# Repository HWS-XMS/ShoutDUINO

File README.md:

# ShoutDUINO

Attention: I still want to place and route the unity gain buffer on the feedback path.
That's not yet in the prod. files.

Arduino-based, safe-ish, EMFI tool, at lower cost.

The board charges a capacitor to a programmable high voltage, then discharges it
through an injection coil on a trigger event. Trigger timing can come from the
host over UART (soft trigger) or from an external trigger input, with host-side
tooling for parameter sweeps.

## Status

**We are currently adding a unity gain buffer to the feedback, which improves
voltage readback.** The buffer isolates the high-voltage divider from the ADC
input, so loading by the converter no longer pulls the measured value down.

This change is in progress and is not yet in the schematic.

## Repository layout

| Path | Contents |
| --- | --- |
| `PCB/` | KiCad project. Root sheet `shoutduino.kicad_sch`, with `charger`, `discharger`, `leds` and `temperature` sub-sheets. |
| `firmware/` | Arduino firmware for the on-board microcontroller. |
| `python/` | Host-side CLI, calibration and experiment scripts. |
| `docs/datasheets/` | Datasheets for the main devices used on the board. |
| `PCB/shoutduino.pretty/`, `PCB/shoutduino.kicad_sym` | Project-local footprint and symbol libraries for the non-stock parts, registered via `PCB/fp-lib-table` and `PCB/sym-lib-table`. |
| `production/` | Generated fabrication output (gerbers, BOM, placement). |
| `DelayUnit/` | Submodule: FPGA-based delay unit used to place the trigger pulse. |

## Hardware

Key devices in the signal chain:

- **LT3751** — flyback controller driving the high-voltage capacitor charger.
- **AD5293** — digital potentiometer setting the charge voltage target.
- **MCP3201** — 12-bit SPI ADC for voltage readback.
- **MCP601** (`U12`) — op-amp in the charger feedback path.
- **TMP117** — temperature monitoring.

The KiCad files are saved in **KiCad 10** format.

## Firmware

Build with `arduino-cli` via the provided Makefile:

```sh
cd firmware
make uno-r4-minima     # or: uno-r4-wifi
make flash             # compile and upload
make detect            # list connected boards
```

Pulse width is constrained to **10–200 ns**. The firmware rejects any soft-trigger
width outside that window, because pulses longer than 200 ns can destroy the
discharge circuit. Note that this guard only covers the UART soft-trigger path —
an externally supplied trigger pulse is not clamped by the firmware.

## Host tooling

```sh
cd python
pip install -r requirements.txt
python emfi_cli.py /dev/ttyACM0     # interactive control
python calibrate.py                 # pot position -> voltage calibration
python experiment.py                # voltage/delay parameter sweep
```

## Cloning

The repository uses a submodule:

```sh
git clone --recurse-submodules https://github.com/HWS-XMS/ShoutDUINO.git
```

## Known issues

- `make uno` (classic AVR Uno) does not compile: `temperature_controller.cpp`
  uses `INPUT_PULLDOWN`, which the AVR core does not provide. Only the UNO R4
  targets build. `make test-all` fails for this reason.

## Safety

This board generates and stores high voltage. The capacitor can hold a dangerous
charge after power is removed. Do not handle the board while it is charged.

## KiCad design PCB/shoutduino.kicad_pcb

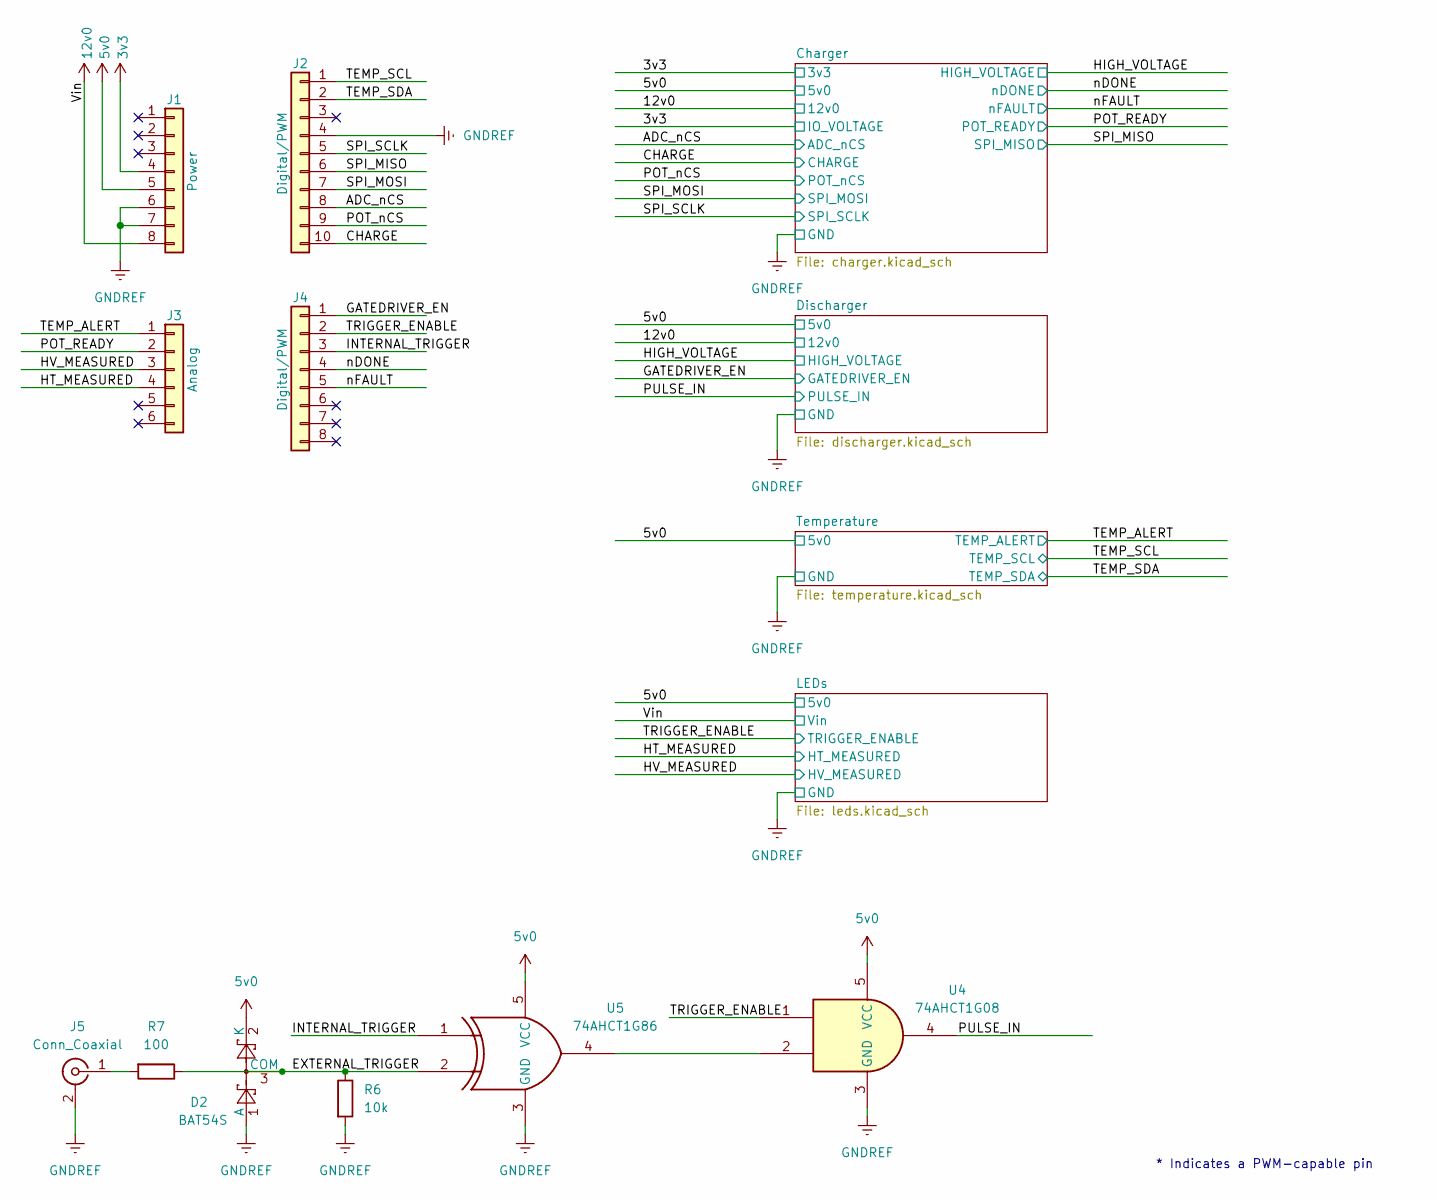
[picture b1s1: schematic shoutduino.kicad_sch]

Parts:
D2: BAT54S; SOT-23
J1: Power; PinSocket_1x08_P2.54mm_Vertical
J2: Digital/PWM; PinSocket_1x10_P2.54mm_Vertical
J3: Analog; PinSocket_1x06_P2.54mm_Vertical
J4: Digital/PWM; PinSocket_1x08_P2.54mm_Vertical
J5: Conn_Coaxial; SMA_Amphenol_132289_EdgeMount
R6: 10k; R_0402_1005Metric
R7: 100; R_0402_1005Metric
U4: 74AHCT1G08; SOT-23-5
U5: 74AHCT1G86; SOT-23-5

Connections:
5v0: D2.2 (K), J1.5, U4.5 (VCC), U5.5 (VCC); also elsewhere on the board
12v0: J1.8; also elsewhere on the board
/ADC_nCS: J2.8; also elsewhere on the board
/CHARGE: J2.10; also elsewhere on the board
/EXTERNAL_TRIGGER: D2.3 (COM), R6.1, R7.1, U5.2
/GATEDRIVER_EN: J4.1; also elsewhere on the board
/HT_MEASURED: J3.4; also elsewhere on the board
/HV_MEASURED: J3.3; also elsewhere on the board
/INTERNAL_TRIGGER: J4.3, U5.1
/POT_READY: J3.2; also elsewhere on the board
/POT_nCS: J2.9; also elsewhere on the board
/PULSE_IN: U4.4; also elsewhere on the board
/SPI_MISO: J2.6; also elsewhere on the board
/SPI_MOSI: J2.7; also elsewhere on the board
/SPI_SCLK: J2.5; also elsewhere on the board
/TEMP_ALERT: J3.1; also elsewhere on the board
/TEMP_SCL: J2.1; also elsewhere on the board
/TEMP_SDA: J2.2; also elsewhere on the board
/TRIGGER_ENABLE: J4.2, U4.1; also elsewhere on the board
/nDONE: J4.4; also elsewhere on the board
/nFAULT: J4.5; also elsewhere on the board
GNDREF: D2.1 (A), J1.6, J1.7, J2.4, J5.2 (Ext), R6.2, U4.3 (GND), U5.3 (GND); also elsewhere on the board
unnamed: J5.1 (In), R7.2
unnamed: U4.2, U5.4

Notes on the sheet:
* Indicates a PWM-capable pin

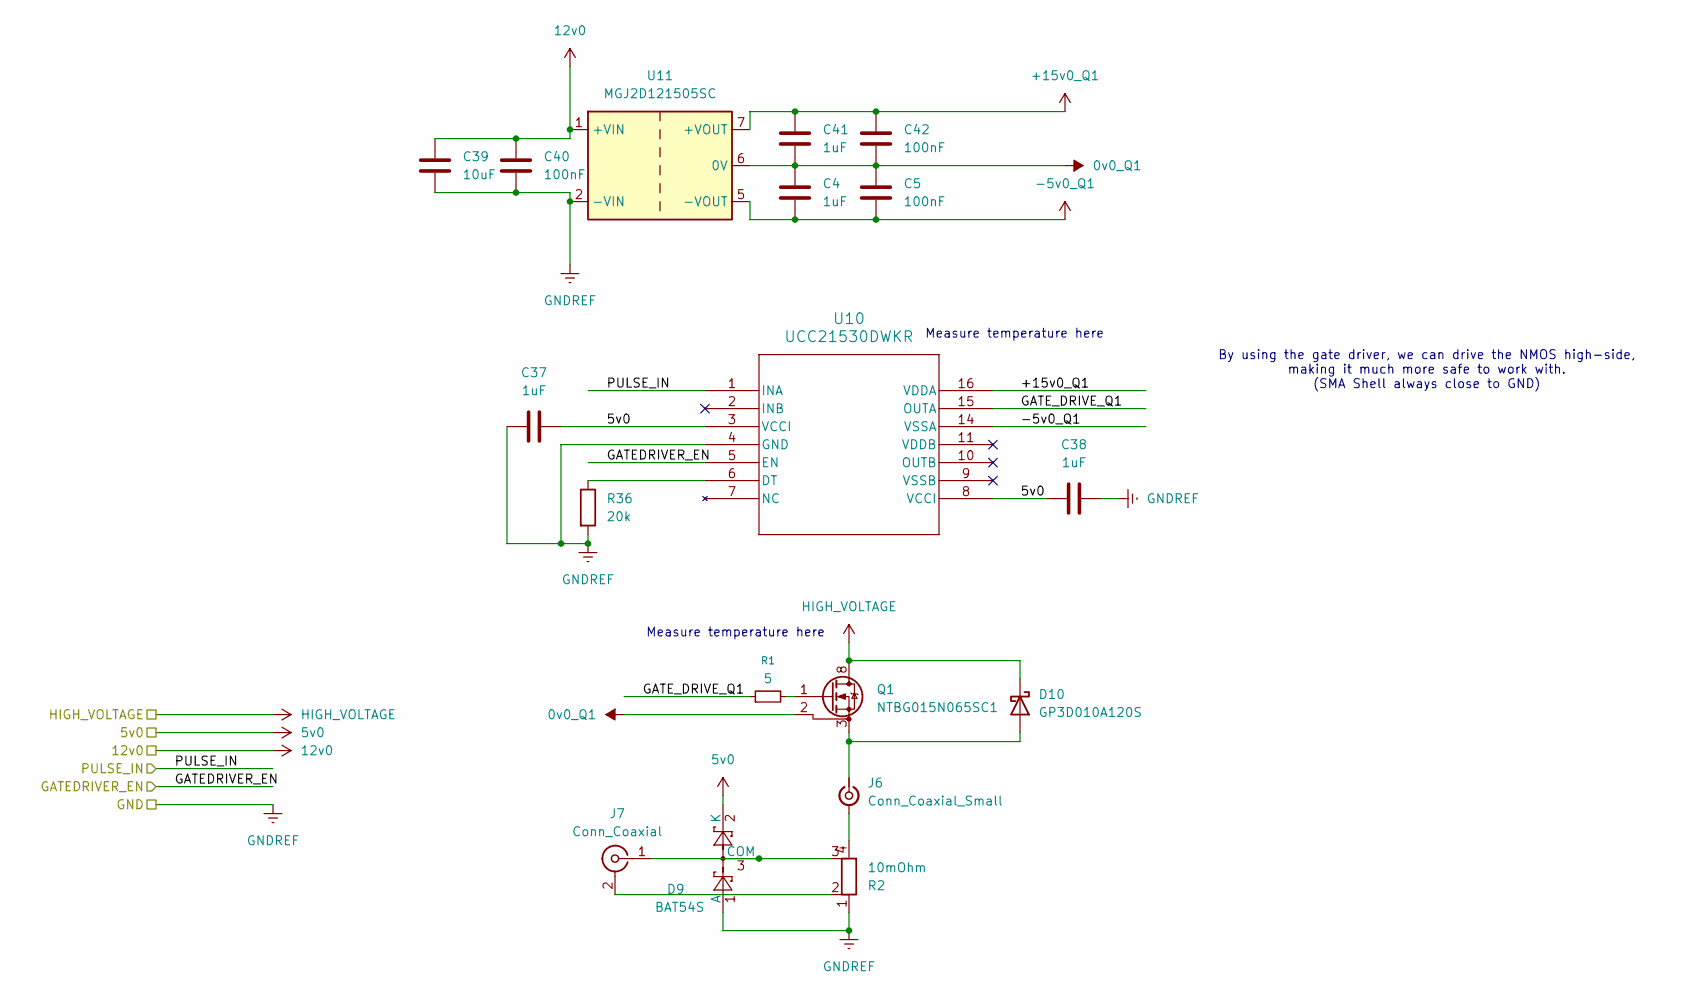
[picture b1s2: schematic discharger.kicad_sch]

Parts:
C4, C37, C38, C41: 1uF; C_0603_1608Metric
C5, C40, C42: 100nF; C_0603_1608Metric
C39: 10uF; C_0603_1608Metric
D9: BAT54S; SOT-23
D10: GP3D010A120S; D_SMC
J6: Conn_Coaxial_Small; SMA_Amphenol_132289_EdgeMount
J7: Conn_Coaxial; U.FL_Molex_MCRF_73412-0110_Vertical
Q1: NTBG015N065SC1; TO-263-7_TabPin8
R1: 5; R_0603_1608Metric
R2: 10mOhm; FC4L110_OHM
R36: 20k; R_0603_1608Metric
U10: UCC21530DWKR; SOIC14_7P6X10P5_TEX
U11: MGJ2D121505SC; Converter_DCDC_Murata_MGJ2DxxxxxxSC_THT

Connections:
0v0_Q1: C4.1, C5.1, C41.2, C42.2, Q1.2 (DS), U11.6 (0V)
5v0: C37.2, C38.2, D9.2 (K), U10.3 (VCCI), U10.8 (VCCI); also elsewhere on the board
12v0: C39.1, C40.1, U11.1 (+VIN); also elsewhere on the board
+15v0_Q1: C41.1, C42.1, U10.16 (VDDA), U11.7 (+VOUT)
-5v0_Q1: C4.2, C5.2, U10.14 (VSSA), U11.5 (-VOUT)
/Discharger/GATE_DRIVE_Q1: R1.1, U10.15 (OUTA)
/GATEDRIVER_EN: U10.5 (EN); also elsewhere on the board
/PULSE_IN: U10.1 (INA); also elsewhere on the board
GNDREF: C37.1, C38.1, C39.2, C40.2, D9.1 (A), R2.1, R36.2, U10.4 (GND), U11.2 (-VIN); also elsewhere on the board
HIGH_VOLTAGE: D10.1 (K), Q1.8 (D); also elsewhere on the board
unnamed: D9.3 (COM), J7.1 (In), R2.3
unnamed: D10.2 (A), J6.1 (In), Q1.3 (S), Q1.4 (S), Q1.5 (S), Q1.6 (S), Q1.7 (S)
unnamed: J6.2 (Ext), R2.4
unnamed: J7.2 (Ext), R2.2
unnamed: Q1.1 (G), R1.2
unnamed: R36.1, U10.6 (DT)

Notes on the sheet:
Measure temperature here
By using the gate driver, we can drive the NMOS high-side, making it much more safe to work with. (SMA Shell always close to GND)

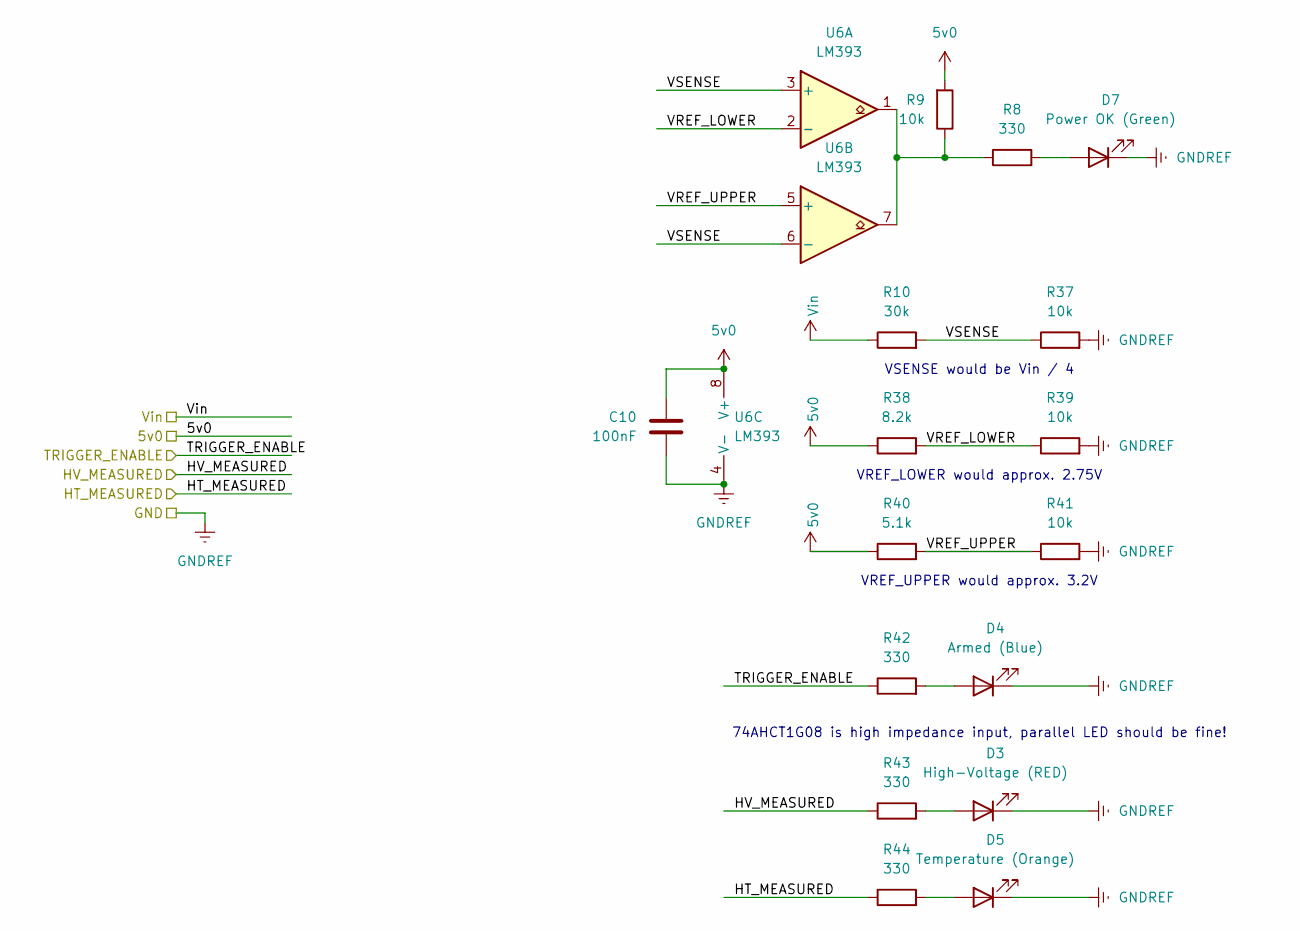
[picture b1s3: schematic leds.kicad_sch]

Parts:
C10: 100nF; C_0603_1608Metric
D3: High-Voltage (RED); LED_0805_2012Metric
D4: Armed (Blue); LED_0805_2012Metric
D5: Temperature (Orange); LED_0805_2012Metric
D7: Power OK (Green); LED_0805_2012Metric
R8, R42, R43, R44: 330; R_0603_1608Metric
R9, R37, R39, R41: 10k; R_0603_1608Metric
R10: 30k; R_0603_1608Metric
R38: 8.2k; R_0603_1608Metric
R40: 5.1k; R_0603_1608Metric
U6: LM393; SOIC-8_3.9x4.9mm_P1.27mm

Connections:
5v0: C10.1, R9.2, R38.1, R40.1, U6.8 (V+); also elsewhere on the board
12v0: R10.1; also elsewhere on the board
/HT_MEASURED: R44.1; also elsewhere on the board
/HV_MEASURED: R43.1; also elsewhere on the board
/LEDs/VREF_LOWER: R38.2, R39.1, U6.2 (-)
/LEDs/VREF_UPPER: R40.2, R41.1, U6.5 (+)
/LEDs/VSENSE: R10.2, R37.1, U6.3 (+), U6.6 (-)
/TRIGGER_ENABLE: R42.1; also elsewhere on the board
GNDREF: C10.2, D3.1 (K), D4.1 (K), D5.1 (K), D7.1 (K), R37.2, R39.2, R41.2, U6.4 (V-); also elsewhere on the board
unnamed: D3.2 (A), R43.2
unnamed: D4.2 (A), R42.2
unnamed: D5.2 (A), R44.2
unnamed: D7.2 (A), R8.2
unnamed: R8.1, R9.1, U6.1, U6.7

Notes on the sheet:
VREF_LOWER would approx. 2.75V
74AHCT1G08 is high impedance input, parallel LED should be fine!
VREF_UPPER would approx. 3.2V
VSENSE would be Vin / 4

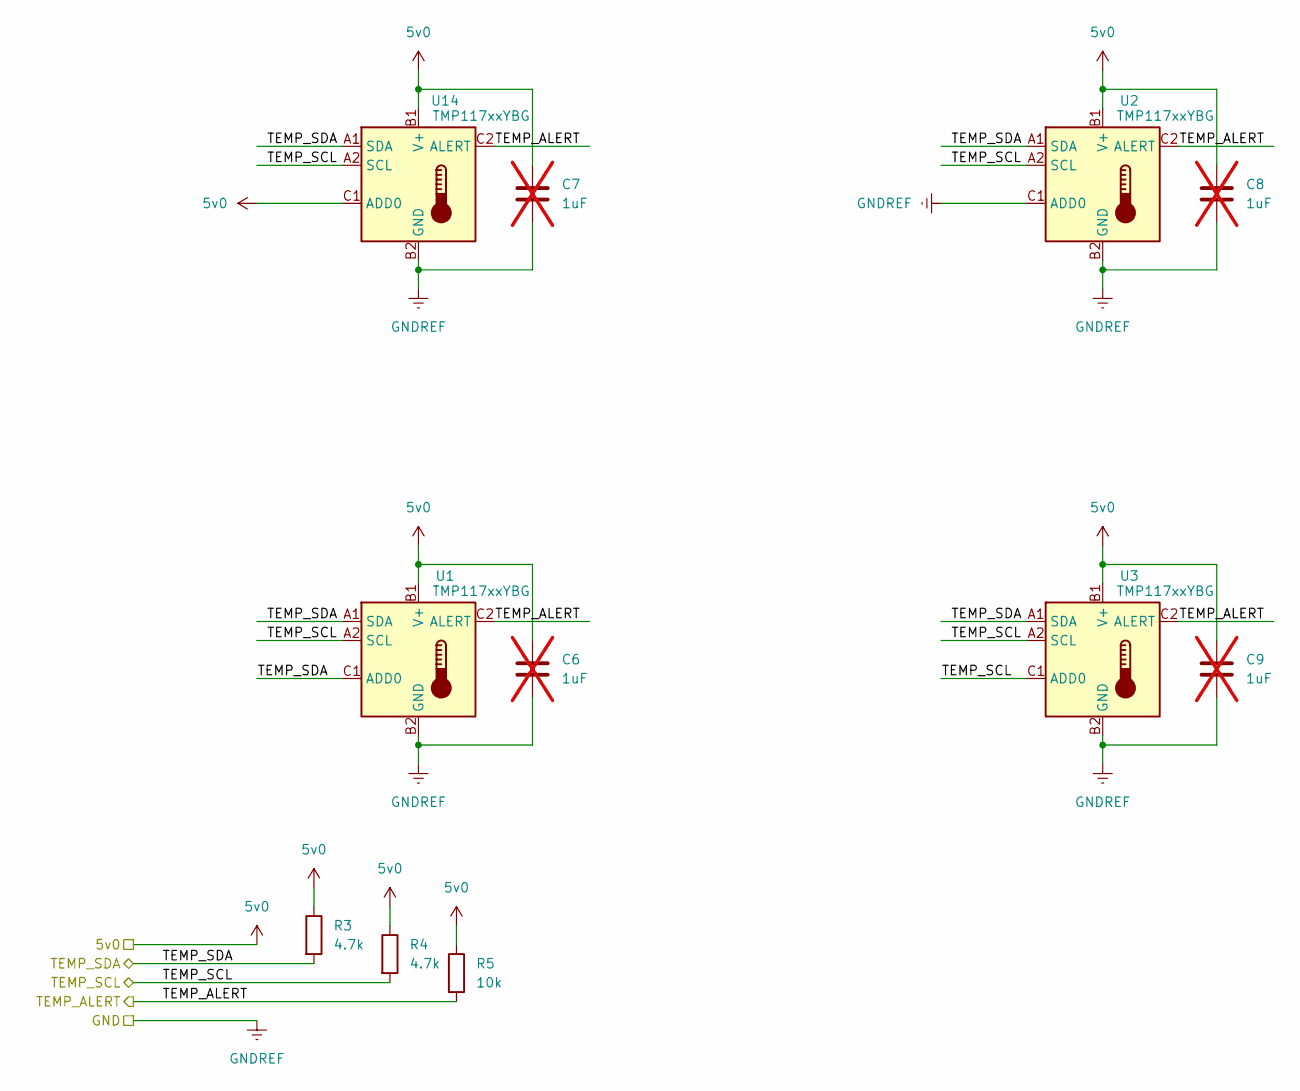
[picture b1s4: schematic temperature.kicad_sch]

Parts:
C6, C7, C8, C9: 1uF; C_0603_1608Metric; not fitted
R3, R4: 4.7k; R_0603_1608Metric
R5: 10k; R_0603_1608Metric
U1, U2, U3, U14: TMP117xxYBG; Texas_DSBGA-6_0.95x1.488mm_Layout2x3_P0.4mm

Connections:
5v0: C6.2, C7.2, C8.2, C9.2, R3.1, R4.1, R5.1, U1.B1 (V+), U2.B1 (V+), U3.B1 (V+), U14.B1 (V+), U14.C1 (ADD0); also elsewhere on the board
/TEMP_ALERT: R5.2, U1.C2 (ALERT), U2.C2 (ALERT), U3.C2 (ALERT), U14.C2 (ALERT); also elsewhere on the board
/TEMP_SCL: R4.2, U1.A2 (SCL), U2.A2 (SCL), U3.A2 (SCL), U3.C1 (ADD0), U14.A2 (SCL); also elsewhere on the board
/TEMP_SDA: R3.2, U1.A1 (SDA), U1.C1 (ADD0), U2.A1 (SDA), U3.A1 (SDA), U14.A1 (SDA); also elsewhere on the board
GNDREF: C6.1, C7.1, C8.1, C9.1, U1.B2 (GND), U2.B2 (GND), U2.C1 (ADD0), U3.B2 (GND), U14.B2 (GND); also elsewhere on the board

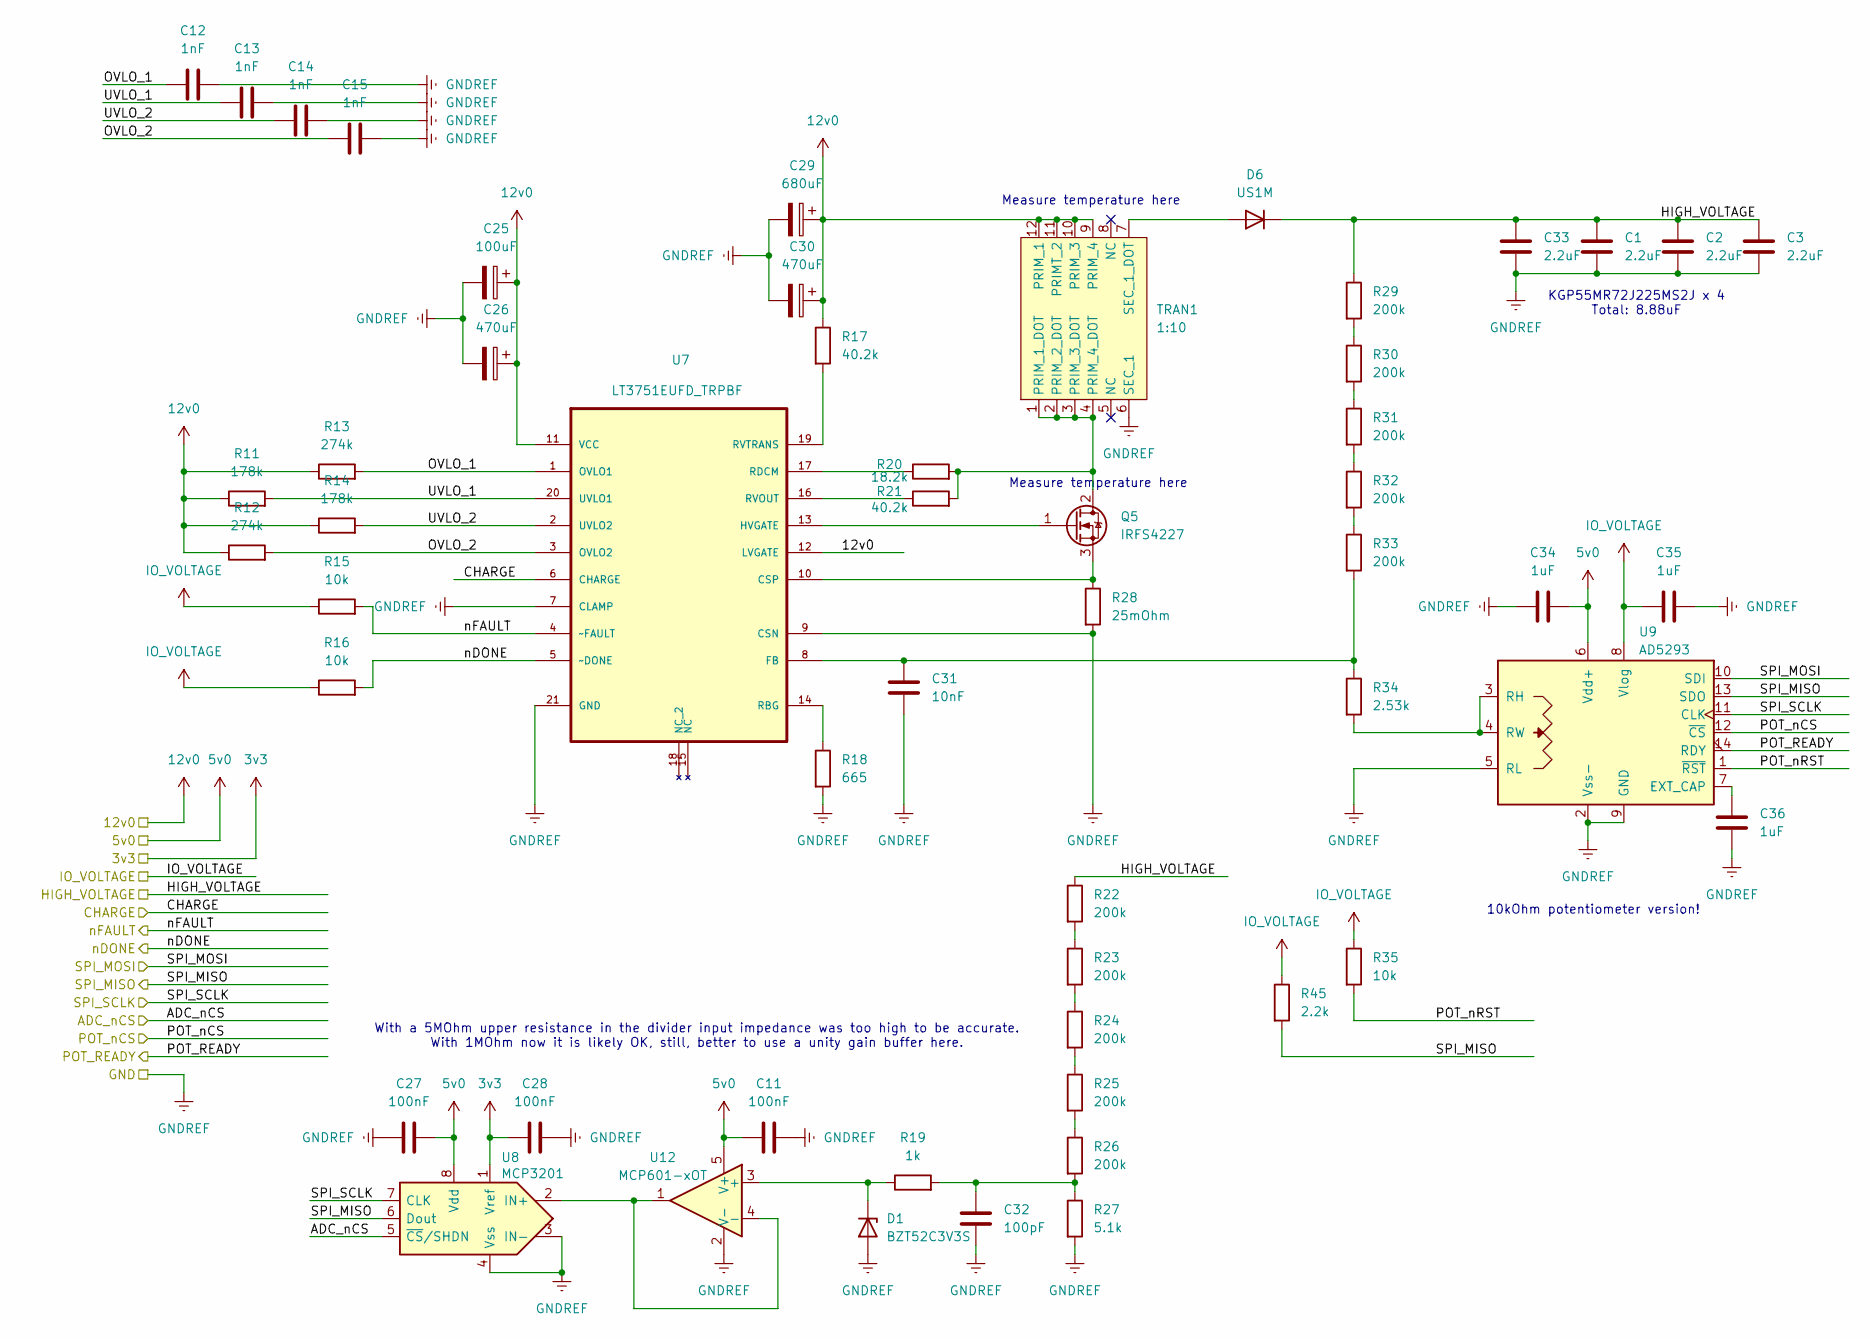
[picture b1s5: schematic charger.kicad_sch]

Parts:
C1, C2, C3, C33: 2.2uF; C_2220_5750Metric
C11, C27, C28: 100nF; C_0603_1608Metric
C12, C13, C14, C15: 1nF; C_0402_1005Metric
C25: 100uF; CP_Radial_D6.3mm_P2.50mm
C26, C30: 470uF; CP_Radial_D8.0mm_P3.50mm
C29: 680uF; CP_Radial_D10.0mm_P5.00mm
C31: 10nF; C_0603_1608Metric
C32: 100pF; C_0603_1608Metric
C34, C35, C36: 1uF; C_0603_1608Metric
D1: BZT52C3V3S; D_SOD-323
D6: US1M; D_SMA
Q5: IRFS4227; TO-263-2
R11, R14: 178k; R_0402_1005Metric
R12, R13: 274k; R_0402_1005Metric
R15, R16: 10k; R_0402_1005Metric
R17: 40.2k; R_0402_1005Metric
R18: 665; R_0603_1608Metric
R19: 1k; R_0603_1608Metric
R20: 18.2k; R_0603_1608Metric
R21: 40.2k; R_0603_1608Metric
R22, R23, R24, R25, R26, R29, R30, R31, R32, R33: 200k; R_0805_2012Metric
R27: 5.1k; R_0805_2012Metric
R28: 25mOhm; R_2512_6332Metric_Pad1.40x3.35mm_HandSolder
R34: 2.53k; R_0805_2012Metric
R35: 10k; R_0603_1608Metric
R45: 2.2k; R_0603_1608Metric
TRAN1: 1:10; GA3460-BL
U7: LT3751EUFD_TRPBF; QFN50P400X500X80-21N; MPN LT3751EUFD#PBF
U8: MCP3201; SOIC-8_3.9x4.9mm_P1.27mm
U9: AD5293; TSSOP-14_4.4x5mm_P0.65mm
U12: MCP601-xOT; SOT-23-5

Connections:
5v0: C11.2, C27.2, C34.2, U8.8 (Vdd), U9.6 (Vdd+), U12.5 (V+); also elsewhere on the board
12v0: C25.1, C26.1, C29.1, C30.1, R11.1, R12.1, R13.1, R14.1, R17.1, TRAN1.9 (PRIM_4), TRAN1.10 (PRIM_3), TRAN1.11 (PRIMT_2), TRAN1.12 (PRIM_1), U7.11 (VCC), U7.12 (LVGATE); also elsewhere on the board
/ADC_nCS: U8.5 (~CS/SHDN); also elsewhere on the board
/CHARGE: U7.6 (CHARGE); also elsewhere on the board
/Charger/OVLO_1: C12.1, R13.2, U7.1 (OVLO1)
/Charger/OVLO_2: C15.1, R12.2, U7.3 (OVLO2)
/Charger/POT_nRST: R35.2, U9.1 (~RST)
/Charger/UVLO_1: C13.1, R11.2, U7.20 (UVLO1)
/Charger/UVLO_2: C14.1, R14.2, U7.2 (UVLO2)
/POT_READY: U9.14 (RDY); also elsewhere on the board
/POT_nCS: U9.12 (~CS); also elsewhere on the board
/SPI_MISO: R45.2, U8.6 (Dout), U9.13 (SDO); also elsewhere on the board
/SPI_MOSI: U9.10 (SDI); also elsewhere on the board
/SPI_SCLK: U8.7 (CLK), U9.11 (CLK); also elsewhere on the board
/nDONE: R16.2, U7.5 (~DONE); also elsewhere on the board
/nFAULT: R15.2, U7.4 (~FAULT); also elsewhere on the board
GNDREF: C1.2, C2.2, C3.2, C11.1, C12.2, C13.2, C14.2, C15.2, C25.2, C26.2, C27.1, C28.1, C29.2, C30.2, C31.2, C32.2, C33.2, C34.1, C35.1, C36.1, D1.2 (A), R18.2, R27.2, R28.2, TRAN1.6 (SEC_1), U7.7 (CLAMP), U7.9 (CSN), U7.21 (GND), U8.3 (IN-), U8.4 (Vss), U9.2 (Vss-), U9.5 (RL), U9.9 (GND), U12.2 (V-); also elsewhere on the board
HIGH_VOLTAGE: C1.1, C2.1, C3.1, C33.1, D6.1 (K), R22.1, R29.1; also elsewhere on the board
unnamed: C32.1, R19.2, R26.2, R27.1
unnamed: D1.1 (K), R19.1, U12.3 (+)
unnamed: D6.2 (A), TRAN1.7 (SEC_1_DOT)
unnamed: Q5.2 (D), R20.2, R21.2, TRAN1.1 (PRIM_1_DOT), TRAN1.2 (PRIM_2_DOT), TRAN1.3 (PRIM_3_DOT), TRAN1.4 (PRIM_4_DOT)
unnamed: Q5.1 (G), U7.13 (HVGATE)
unnamed: Q5.3 (S), R28.1, U7.10 (CSP)
unnamed: R22.2, R23.1
unnamed: R23.2, R24.1
unnamed: R24.2, R25.1
unnamed: R25.2, R26.1
unnamed: R29.2, R30.1
unnamed: R30.2, R31.1
unnamed: R31.2, R32.1
unnamed: R32.2, R33.1
unnamed: C31.1, R33.2, R34.1, U7.8 (FB)
unnamed: R18.1, U7.14 (RBG)
unnamed: R20.1, U7.17 (RDCM)
unnamed: R21.1, U7.16 (RVOUT)
unnamed: R17.2, U7.19 (RVTRANS)
unnamed: C36.2, U9.7 (EXT_CAP)
unnamed: R34.2, U9.3 (RH), U9.4 (RW)
unnamed: U8.2 (IN+), U12.1, U12.4 (-)

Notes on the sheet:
KGP55MR72J225MS2J x 4 Total: 8.88uF
With a 5MOhm upper resistance in the divider input impedance was too high to be accurate. With 1MOhm now it is likely OK, still, better to use a unity gain buffer here.
Measure temperature here
10kOhm potentiometer version!

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
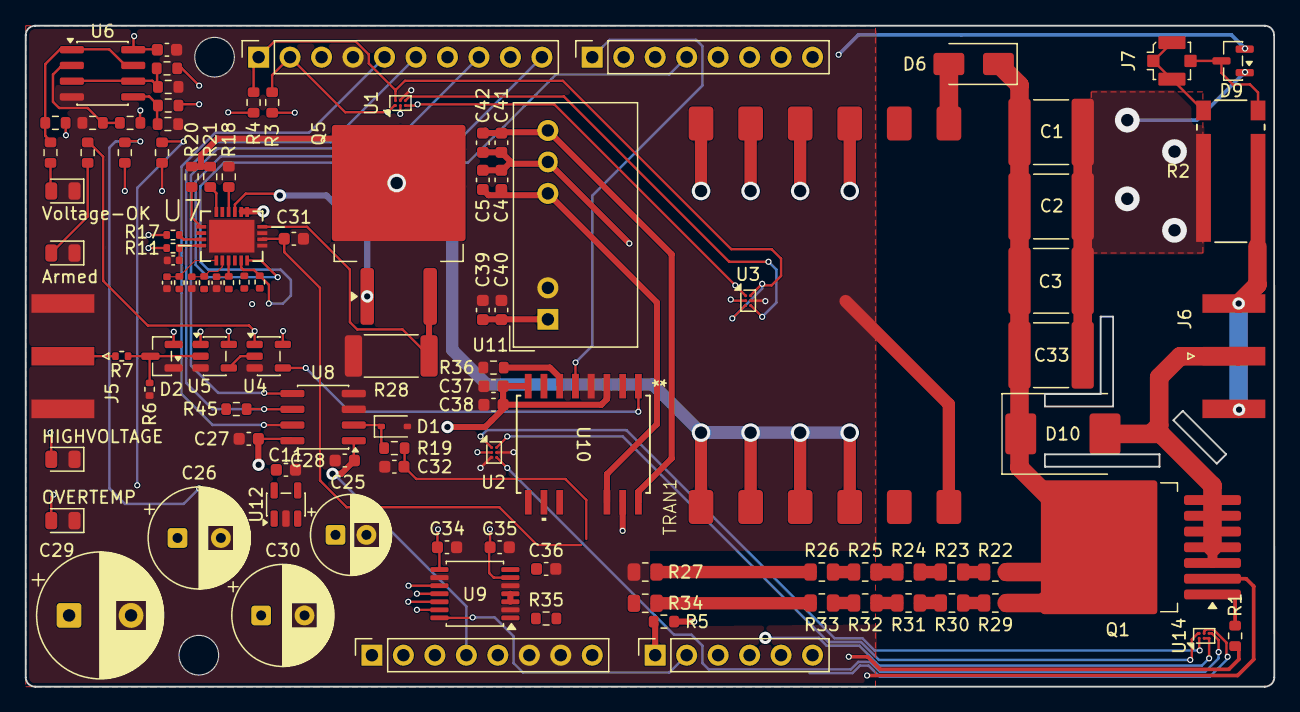
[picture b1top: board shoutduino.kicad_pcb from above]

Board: 4 copper layers, 100.8 x 53.3 mm, 108 parts (0 on the bottom side), 71 nets.

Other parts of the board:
MH1, MH2: MountingHole_3.2mm

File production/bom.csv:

Designator,Footprint,Quantity,Value,LCSC Part #
"C1, C2, C3, C33",2220,4,2.2uF,
"C10, C27, C28, C40, C42, C5",0603,6,100nF,
C25,CP_Radial_D6.3mm_P2.50mm,1,100uF,
"C26, C30",CP_Radial_D8.0mm_P3.50mm,2,470uF,
C29,CP_Radial_D10.0mm_P5.00mm,1,680uF,
C31,0603,1,10nF,
C32,0603,1,100pF,
"C34, C35, C36, C37, C38, C4, C41",0603,7,1uF,
C39,0603,1,10uF,
D1,D_SOD-323,1,BZT52C3V3S,
"D2, D9",SOT-23,2,BAT54S,
D3,0805,1,High-Voltage (RED),
D4,0805,1,Armed (Blue),
D5,0805,1,Temperature (Orange),
"D6, D8",D_SMA,2,US1M,
D7,0805,1,Power OK (Green),
J1,PinSocket_1x08_P2.54mm_Vertical,1,Power,
J2,PinSocket_1x10_P2.54mm_Vertical,1,Digital/PWM,
J3,PinSocket_1x06_P2.54mm_Vertical,1,Analog,
J4,PinSocket_1x08_P2.54mm_Vertical,1,Digital/PWM,
J5,SMA_Amphenol_132289_EdgeMount,1,Conn_Coaxial,
J6,SMA_Amphenol_132289_EdgeMount,1,Conn_Coaxial_Small,
J7,U.FL_Molex_MCRF_73412-0110_Vertical,1,Conn_Coaxial,
Q1,TO-263-7_TabPin8,1,NTBG015N065SC1,
Q5,TO-263-2,1,IRFS4227,
R1,0603,1,10,
R10,0603,1,30k,
"R11, R14",0402,2,178k,
"R12, R13",0402,2,274k,
"R15, R16, R6",0402,3,10k,
R17,0402,1,40.2k,
R18,0603,1,665,
R19,0603,1,1k,
R2,FC4L110_OHM,1,10mOhm,
R20,0603,1,18.2k,
R21,0603,1,40.2k,
"R22, R23, R24, R25, R26, R29, R30, R31, R32, R33",0805,10,1M,
R27,0805,1,25k,
R28,2512,1,25mOhm,
"R3, R4",0603,2,4.7k,
R34,0805,1,12.1k,
"R35, R37, R39, R41, R5, R9",0603,6,10k,
R36,0603,1,20k,
R38,0603,1,8.2k,
R40,0603,1,5.1k,
"R42, R43, R44, R8",0603,4,330,
R7,0402,1,100,
TRAN1,GA3460-BL,1,1:10,
"U1, U14, U2, U3",Texas_DSBGA-6_0.95x1.488mm_Layout2x3_P0.4mm,4,TMP117xxYBG,
U10,SOIC14_7P6X10P5_TEX,1,UCC21530DWKR,
U11,Converter_DCDC_Murata_MGJ2DxxxxxxSC_THT,1,MGJ2D121505SC,
U4,SOT-23-5,1,74AHCT1G08,
U5,SOT-23-5,1,74AHCT1G86,
U6,SOIC-8_3.9x4.9mm_P1.27mm,1,LM393,
U7,QFN50P400X500X80-21N,1,LT3751EUFD_TRPBF,LT3751EUFD#PBF
U8,SOIC-8_3.9x4.9mm_P1.27mm,1,MCP3201,
U9,TSSOP-14_4.4x5mm_P0.65mm,1,AD5293,

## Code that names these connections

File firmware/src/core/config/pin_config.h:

/**
Pin Assignment Summary:
    Digital Pins:
    Pin 3  - LT3751_nFAULT    (Input, active low)
    Pin 4  - LT3751_nDONE     (Input, active low)
    Pin 5  - INTERNAL_TRIGGER (Output, pulse generation)
    Pin 6  - TRIGGER_ENABLE   (Output, active high)
    Pin 7  - GATEDRIVER_EN    (Output, active high)
    Pin 8  - CHARGE           (Output, active high)
    Pin 9  - POT_nCS          (Output, SPI chip select)
    Pin 10 - ADC_nCS          (Output, SPI chip select)
    Pin 11 - MOSI             (Output, SPI data)
    Pin 12 - MISO             (Input, SPI data)
    Pin 13 - SCK              (Output, SPI clock)

    Analog Pins:
    A0     - TEMP_ALERT       (Input, active high)
    A1     - POT_READY        (Input, active high)
    A2     - HT_MEASURED      (Output, LED control)
    A3     - HV_MEASURED      (Output, LED control)
    A4     - SDA              (I2C data, bidirectional)
    A5     - SCL              (I2C clock, output)
*/

#ifndef PIN_CONFIG_H
#define PIN_CONFIG_H

// Digital Pins
#define LT3751_nFAULT_PIN       3
#define LT3751_nDONE_PIN        4
#define PULSE_GENERATOR_PIN     5       // INTERNAL_TRIGGER
#define TRIGGER_ENABLE_PIN      6
#define GATE_DRIVER_EN_PIN      7       // GATEDRIVER_EN
#define LT3751_CHARGE_PIN       8       // CHARGE
#define AD5293_CS_PIN           9       // POT_nCS
#define MCP3201_CS_PIN          10      // ADC_nCS
#define SPI_MOSI_PIN            11
#define SPI_MISO_PIN            12
#define SPI_SCK_PIN             13      // SPI_CLK

// Analog Pins
#define TEMP_ALERT_PIN          A0
#define POT_READY_PIN           A1
#define LED_HV_MEASURED_PIN     A2      // HV_MEASURED (Voltage > 10V)
#define LED_HT_MEASURED_PIN     A3      // HT_MEASURED (Temperature high)
#define I2C_SDA_PIN             A4      // TEMP_SDA
#define I2C_SCL_PIN             A5      // TEMP_SCL

#endif // PIN_CONFIG_H
